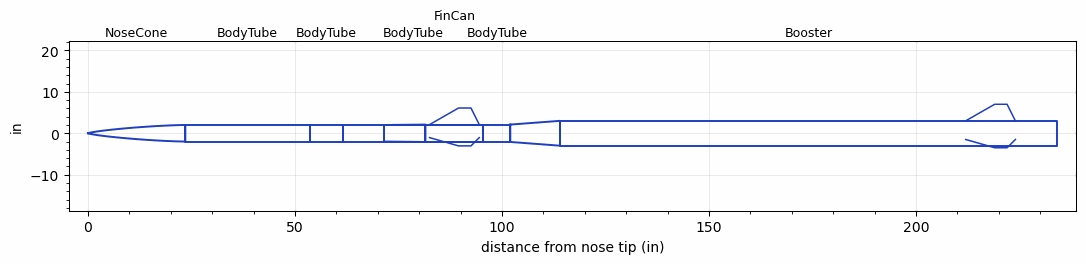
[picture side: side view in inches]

<RASAeroDocument>
 <FileVersion>2</FileVersion>
 <RocketDesign>
  <NoseCone>
   <Length>23.5</Length>
   <Diameter>4</Diameter>
   <Shape>Von Karman Ogive</Shape>
   <Location>0</Location>
  </NoseCone>
  <BodyTube>
   <Length>30</Length>
   <Diameter>4</Diameter>
   <Location>23.5</Location>
  </BodyTube>
  <BodyTube>
   <Length>8</Length>
   <Diameter>4</Diameter>
   <Location>53.5</Location>
  </BodyTube>
  <BodyTube>
   <Length>34</Length>
   <Diameter>4</Diameter>
   <Location>61.5</Location>
  </BodyTube>
  <FinCan>
   <Length>14</Length>
   <Diameter>4.2</Diameter>
   <InsideDiameter>4</InsideDiameter>
   <Location>95.5</Location>
   <ShoulderLength>10</ShoulderLength>
   <Offset>-14</Offset>
   <Fin>
    <Count>3</Count>
    <Chord>12</Chord>
    <Span>4</Span>
    <SweepDistance>7</SweepDistance>
    <TipChord>3</TipChord>
    <Thickness>0.2</Thickness>
    <LERadius>0.03</LERadius>
    <Location>13</Location>
    <AirfoilSection>Double Wedge</AirfoilSection>
    <FX1>3.75</FX1>
    <FX3>6</FX3>
   </Fin>
  </FinCan>
  <BodyTube>
   <Length>6.5</Length>
   <Diameter>4.2</Diameter>
   <Location>95.5</Location>
  </BodyTube>
  <Booster>
   <Length>120</Length>
   <Diameter>6</Diameter>
   <InsideDiameter>4.2</InsideDiameter>
   <Location>102</Location>
   <ShoulderLength>12</ShoulderLength>
   <Fin>
    <Count>3</Count>
    <Chord>12</Chord>
    <Span>4</Span>
    <SweepDistance>7</SweepDistance>
    <TipChord>3</TipChord>
    <Thickness>0.25</Thickness>
    <LERadius>0.03</LERadius>
    <Location>22</Location>
    <AirfoilSection>Double Wedge</AirfoilSection>
    <FX1>3.75</FX1>
    <FX3>3.75</FX3>
   </Fin>
  </Booster>
  <Surface>Smooth (Zero Roughness)</Surface>
  <ModifiedBarrowman>False</ModifiedBarrowman>
  <Turbulence>False</Turbulence>
  <UseBooster1>True</UseBooster1>
  <UseBooster2>False</UseBooster2>
 </RocketDesign>
 <LaunchSite>
  <Altitude>3000</Altitude>
  <Pressure>30.3</Pressure>
  <RodAngle>1</RodAngle>
  <RodLength>25</RodLength>
  <Temperature>90</Temperature>
  <WindSpeed>12</WindSpeed>
 </LaunchSite>
 <Recovery>
  <Altitude1>1000</Altitude1>
  <Altitude2>1000</Altitude2>
  <DeviceType1>None</DeviceType1>
  <DeviceType2>None</DeviceType2>
  <Event1>False</Event1>
  <Event2>False</Event2>
  <Size1>1</Size1>
  <Size2>1</Size2>
  <EventType1>None</EventType1>
  <EventType2>None</EventType2>
  <CD1>1.33</CD1>
  <CD2>1.33</CD2>
 </Recovery>
 <SimulationList>
  <Simulation>
   <SustainerEngine>BERMA-25000-01  (Karman_AIAA-capstone)</SustainerEngine>
   <SustainerLaunchWt>35</SustainerLaunchWt>
   <SustainerNozzleDiameter>3.8</SustainerNozzleDiameter>
   <SustainerCG>57.59</SustainerCG>
   <SustainerIgnitionDelay>0</SustainerIgnitionDelay>
   <Booster1Engine>O8000  (CTI)</Booster1Engine>
   <Booster1LaunchWt>150</Booster1LaunchWt>
   <Booster1SeparationDelay>0</Booster1SeparationDelay>
   <Booster1IgnitionDelay>0</Booster1IgnitionDelay>
   <Booster1CG>105</Booster1CG>
   <Booster1NozzleDiameter>5.8</Booster1NozzleDiameter>
   <IncludeBooster1>True</IncludeBooster1>
   <Booster2Delay>0</Booster2Delay>
   <IncludeBooster2>False</IncludeBooster2>
   <TimetoApogee>13.46012</TimetoApogee>
   <MaxAltitude>64206.91</MaxAltitude>
   <MaxVelocity>11443.72</MaxVelocity>
  </Simulation>
 </SimulationList>
</RASAeroDocument>
